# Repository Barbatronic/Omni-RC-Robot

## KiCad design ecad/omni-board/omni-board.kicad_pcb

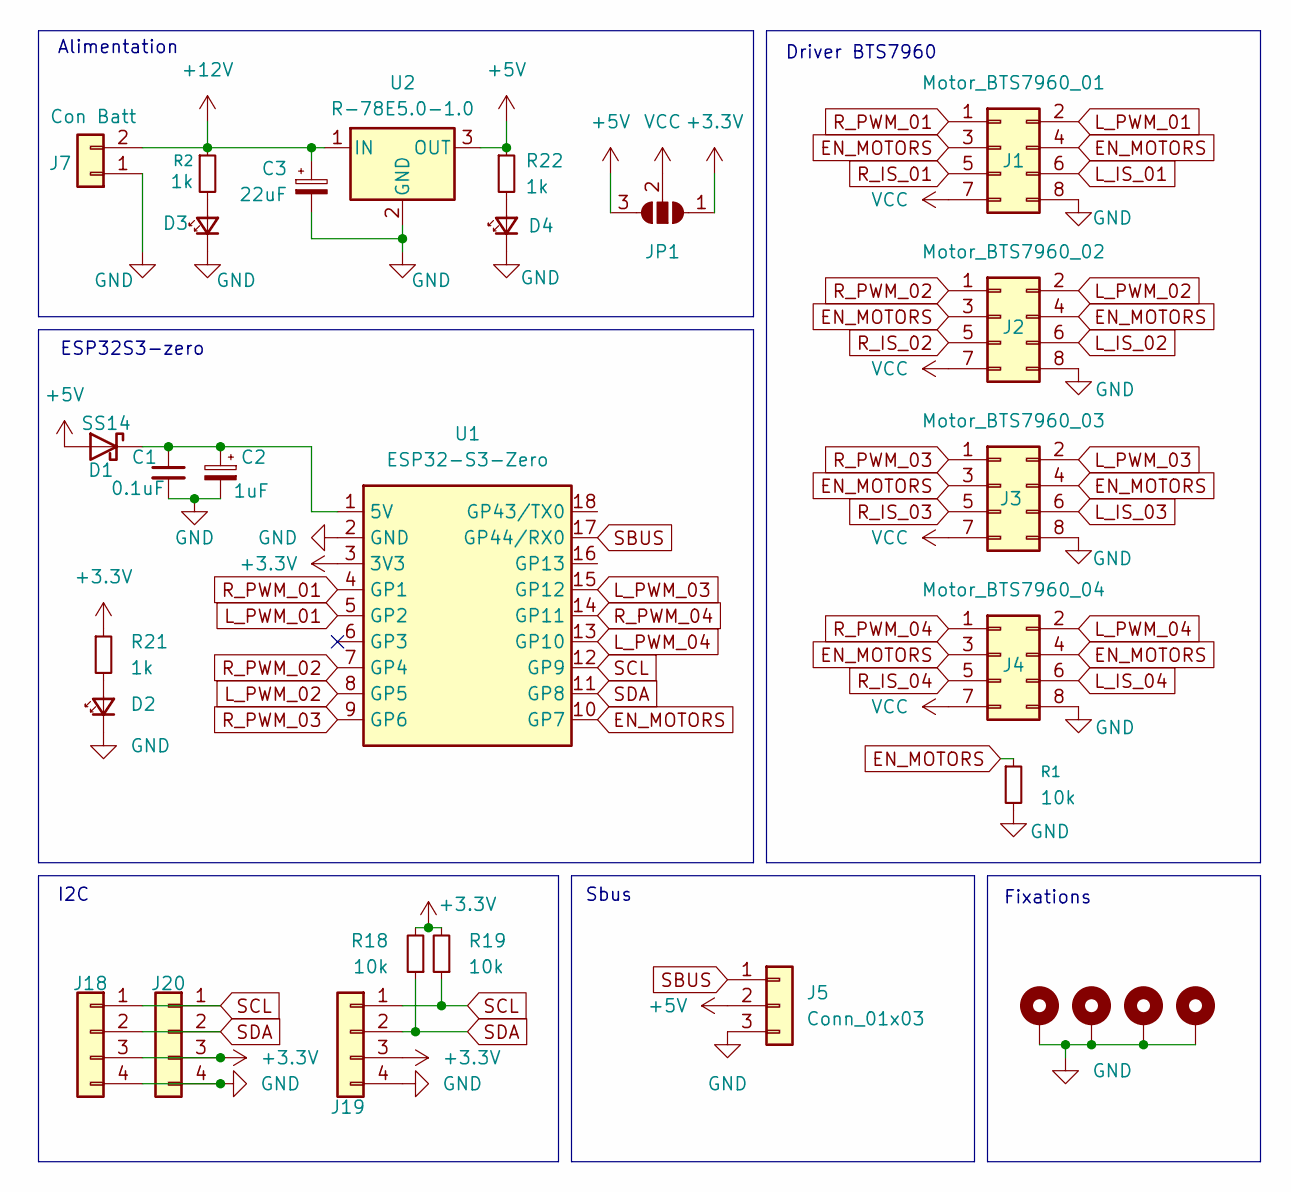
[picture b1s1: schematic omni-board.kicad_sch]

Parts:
C1: 0.1uF; C_1206_3216Metric_Pad1.33x1.80mm_HandSolder
C2: 1uF; CP_Elec_5x5.4
C3: 22uF; CP_Elec_5x5.4
D1: SS14; D_SMA_Handsoldering
D2, D3, D4: LED_Small; LED_1206_3216Metric_Pad1.42x1.75mm_HandSolder
H1, H2, H3, H4: MountingHole_Pad; MountingHole_3.2mm_M3_Pad_Via
J1: Motor_BTS7960_01; IDC-Header_2x04_P2.54mm_Vertical
J2: Motor_BTS7960_02; IDC-Header_2x04_P2.54mm_Vertical
J3: Motor_BTS7960_03; IDC-Header_2x04_P2.54mm_Vertical
J4: Motor_BTS7960_04; IDC-Header_2x04_P2.54mm_Vertical
J5: Conn_01x03; PinHeader_1x03_P2.54mm_Vertical
J7: Con Batt; AMASS_XT60-M_1x02_P7.20mm_Vertical
J18, J19, J20: Conn_01x04; Molex_KK-254_AE-6410-04A_1x04_P2.54mm_Vertical
JP1: SolderJumper_3_Open; SolderJumper-3_P2.0mm_Open_TrianglePad1.0x1.5mm
R1, R18, R19: 10k; R_1206_3216Metric_Pad1.30x1.75mm_HandSolder
R2, R21, R22: 1k; R_1206_3216Metric_Pad1.30x1.75mm_HandSolder
U1: ESP32-S3-Zero; ESP32-S3-Zero_THT; MPN ESP32-S3-Zero
U2: R-78E5.0-1.0; Converter_DCDC_RECOM_R-78E-0.5_THT

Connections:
+3.3V: J18.3, J19.3, J20.3, JP1.1 (A), R18.2, R19.2, R21.1, U1.3 (3V3)
+5V: D1.2 (A), J5.2, JP1.3 (B), R22.1, U2.3 (OUT)
+12V: C3.1, J7.2, R2.1, U2.1 (IN)
EN_MOTORS: J1.3, J1.4, J2.3, J2.4, J3.3, J3.4, J4.3, J4.4, R1.1, U1.10 (GP7)
GND: C1.2, C2.2, C3.2, D2.1 (K), D3.1 (K), D4.1 (K), H1.1 (1_1), H2.1 (1_1), H3.1 (1_1), H4.1 (1_1), J1.8, J2.8, J3.8, J4.8, J5.3, J7.1, J18.4, J19.4, J20.4, R1.2, U1.2 (GND), U2.2 (GND)
L_IS_01: J1.6
L_IS_02: J2.6
L_IS_03: J3.6
L_IS_04: J4.6
L_PWM_01: J1.2, U1.5 (GP2)
L_PWM_02: J2.2, U1.8 (GP5)
L_PWM_03: J3.2, U1.15 (GP12)
L_PWM_04: J4.2, U1.13 (GP10)
unnamed: C1.1, C2.1, D1.1 (K), U1.1 (5V)
unnamed: D2.2 (A), R21.2
unnamed: D3.2 (A), R2.2
unnamed: D4.2 (A), R22.2
R_IS_01: J1.5
R_IS_02: J2.5
R_IS_03: J3.5
R_IS_04: J4.5
R_PWM_01: J1.1, U1.4 (GP1)
R_PWM_02: J2.1, U1.7 (GP4)
R_PWM_03: J3.1, U1.9 (GP6)
R_PWM_04: J4.1, U1.14 (GP11)
SBUS: J5.1, U1.17 (GP44/RX0)
SCL: J18.1, J19.1, J20.1, R19.1, U1.12 (GP9)
SDA: J18.2, J19.2, J20.2, R18.1, U1.11 (GP8)
VCC: J1.7, J2.7, J3.7, J4.7, JP1.2 (C)

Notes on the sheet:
Fixations
Driver BTS7960
Sbus
ESP32S3-zero
Alimentation
I2C

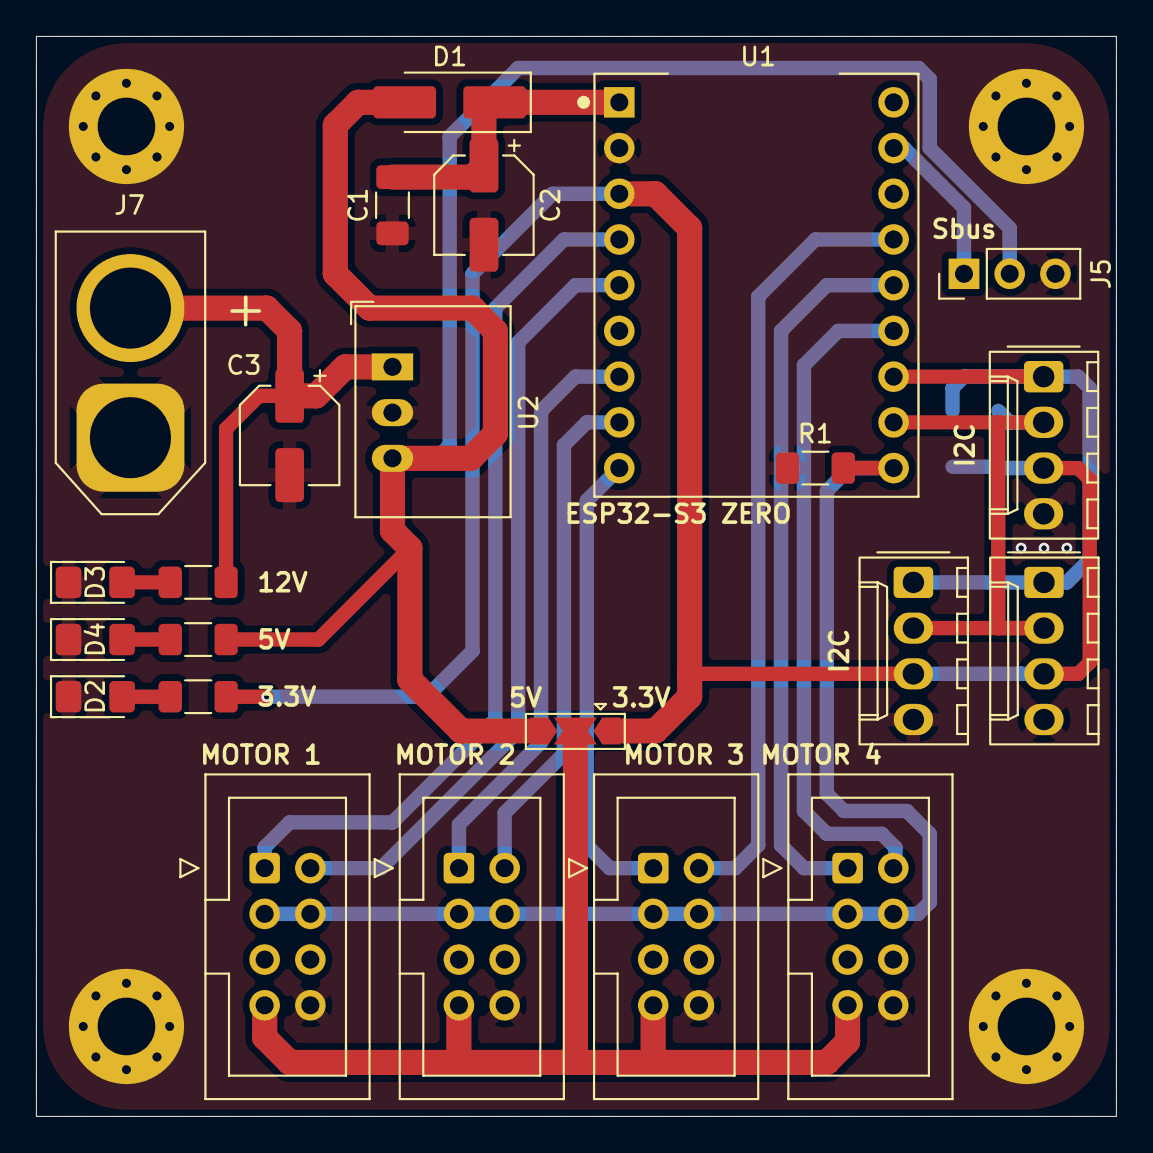
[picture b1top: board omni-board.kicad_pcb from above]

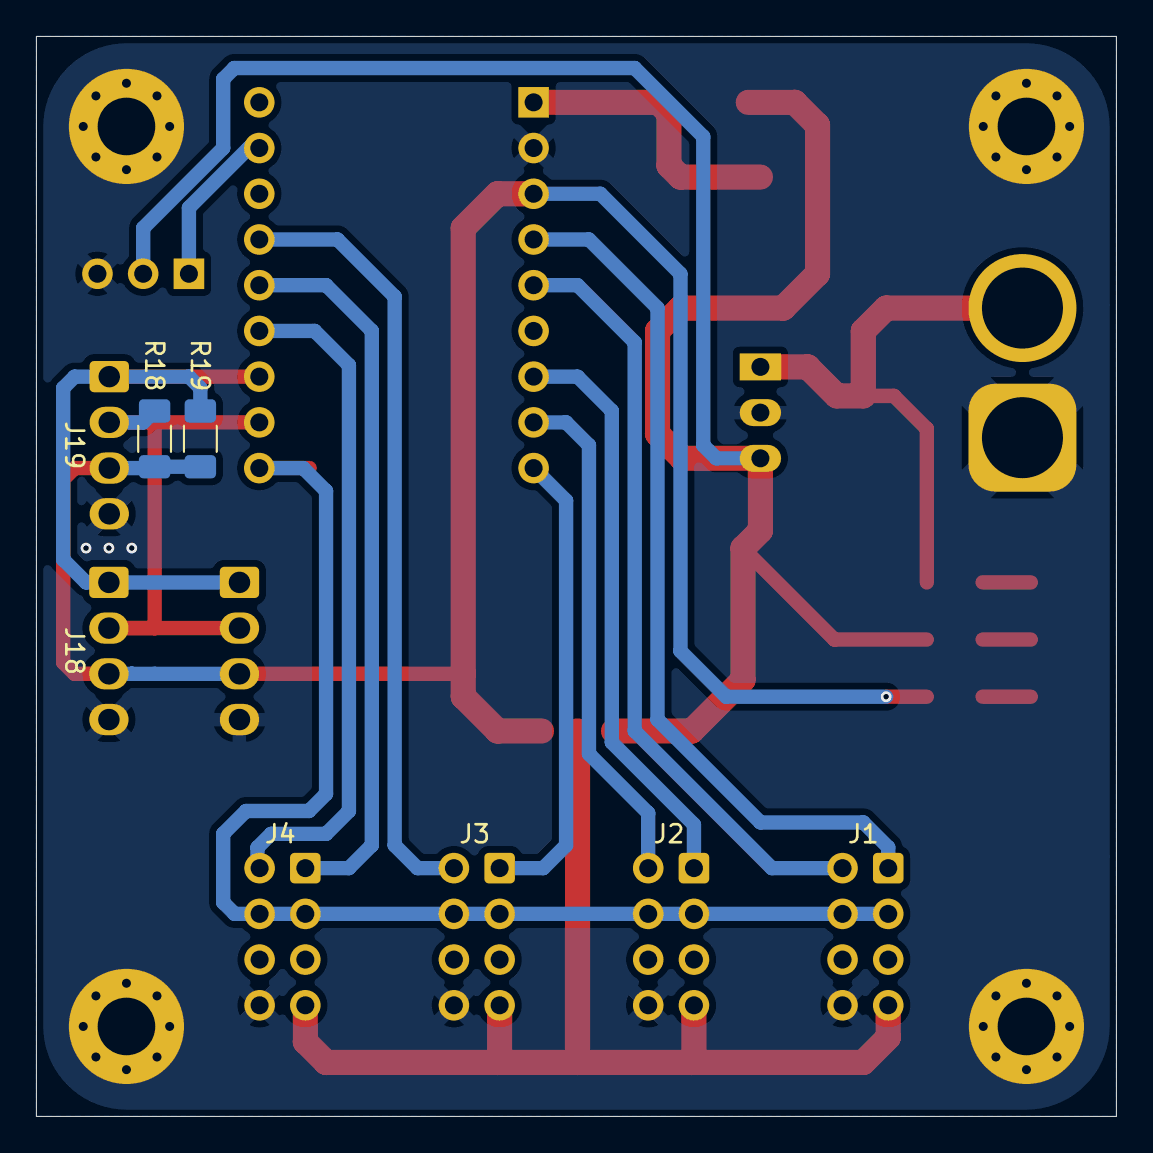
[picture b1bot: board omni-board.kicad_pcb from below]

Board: 2 copper layers, 60.0 x 60.0 mm, 29 parts (2 on the bottom side), 21 nets.
